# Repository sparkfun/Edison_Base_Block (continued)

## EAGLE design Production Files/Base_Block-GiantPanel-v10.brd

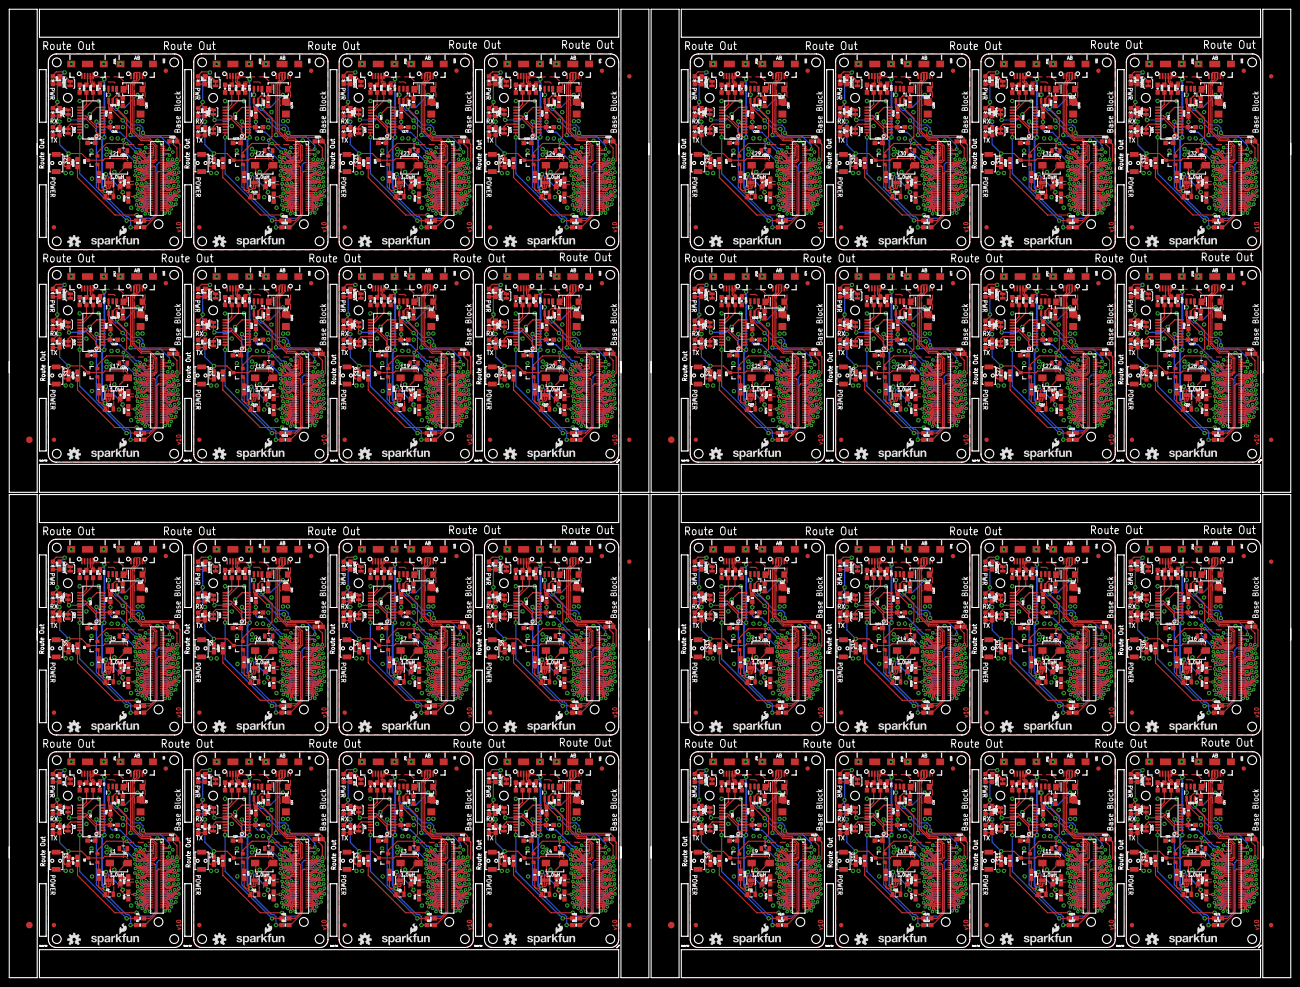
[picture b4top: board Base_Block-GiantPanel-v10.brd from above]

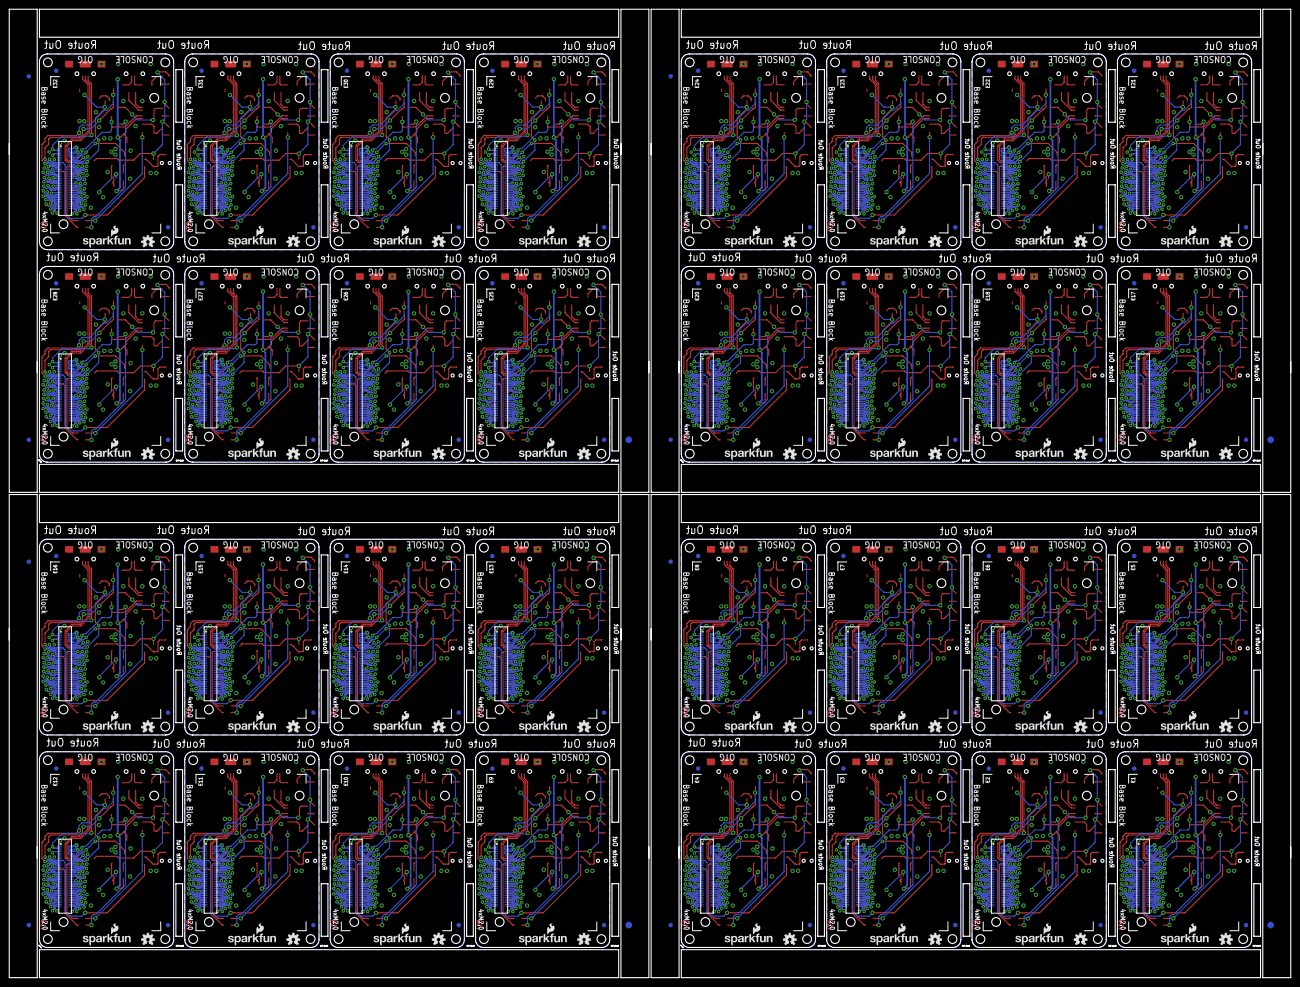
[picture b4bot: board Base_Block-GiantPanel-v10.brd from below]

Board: 2 copper layers, 291.1 x 220.0 mm, 1560 parts (204 on the bottom side), 2496 nets.

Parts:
C1, C2, C5, C10, C17, C18, C25, C26, C33, C34, C41, C42, C49, C50, C57, C58, C65, C66, C73, C74, C81, C82, C89, C90, C97, C98, C105, C106, C113, C114, C121, C122, C129, C130, C137, C138, C145, C146, C153, C154, C161, C162, C169, C170, C177, C178, C185, C186, C193, C194, C201, C202, C209, C210, C217, C218, C225, C226, C233, C234, C241, C242, C249, C250: 0.1uF; 0603-CAP
C3, C4, C7, C11, C12, C15, C19, C20, C23, C27, C28, C31, C35, C36, C39, C43, C44, C47, C51, C52, C55, C59, C60, C63, C67, C68, C71, C75, C76, C79, C83, C84, C87, C91, C92, C95, C99, C100, C103, C107, C108, C111, C115, C116, C119, C123, C124, C127, C131, C132, C135, C139, C140, C143, C147, C148, C151, C155, C156, C159, C163, C164, C167, C171, C172, C175, C179, C180, C183, C187, C188, C191, C195, C196, C199, C203, C204, C207, C211, C212, C215, C219, C220, C223, C227, C228, C231, C235, C236, C239, C243, C244, C247, C251, C252, C255: 47pF; 0603-CAP
C6, C9, C13, C16, C21, C24, C29, C32, C37, C40, C45, C48, C53, C56, C61, C64, C69, C72, C77, C80, C85, C88, C93, C96, C101, C104, C109, C112, C117, C120, C125, C128, C133, C136, C141, C144, C149, C152, C157, C160, C165, C168, C173, C176, C181, C184, C189, C192, C197, C200, C205, C208, C213, C216, C221, C224, C229, C232, C237, C240, C245, C248, C253, C256: 22uF; 0805
C8, C14, C22, C30, C38, C46, C54, C62, C70, C78, C86, C94, C102, C110, C118, C126, C134, C142, C150, C158, C166, C174, C182, C190, C198, C206, C214, C222, C230, C238, C246, C254: 10uF; 1206
D1, D5, D9, D13, D17, D21, D25, D29, D33, D37, D41, D45, D49, D53, D57, D61, D65, D69, D73, D77, D81, D85, D89, D93, D97, D101, D105, D109, D113, D117, D121, D125: RED; LED-0603
D2, D6, D10, D14, D18, D22, D26, D30, D34, D38, D42, D46, D50, D54, D58, D62, D66, D70, D74, D78, D82, D86, D90, D94, D98, D102, D106, D110, D114, D118, D122, D126: YELLOW; LED-0603
D3, D7, D11, D15, D19, D23, D27, D31, D35, D39, D43, D47, D51, D55, D59, D63, D67, D71, D75, D79, D83, D87, D91, D95, D99, D103, D107, D111, D115, D119, D123, D127: BLUE; LED-0603
D4, D8, D12, D16, D20, D24, D28, D32, D36, D40, D44, D48, D52, D56, D60, D64, D68, D72, D76, D80, D84, D88, D92, D96, D100, D104, D108, D112, D116, D120, D124, D128: SMA-DIODE
E1, E2, E3, E4, E5, E6, E7, E8, E9, E10, E11, E12, E13, E14, E15, E16, E17, E18, E19, E20, E21, E22, E23, E24, E25, E26, E27, E28, E29, E30, E31, E32: EDISON_CONNECTOR_FULLMOUNTING_HOLES; EDISON_DAUGHTER
E$1, E$2, E$9, E$10, E$15, E$16, E$21, E$22: FIDUCIAL-1.5X3
E$3, E$4, E$5, E$6, E$7, E$8, E$11, E$12, E$13, E$14, E$17, E$18, E$19, E$20, E$23, E$24: FIDUCIAL-1X2
FID1, FID2, FID3, FID4, FID5, FID6, FID7, FID8, FID9, FID10, FID11, FID12, FID13, FID14, FID15, FID16, FID17, FID18, FID19, FID20, FID21, FID22, FID23, FID24, FID25, FID26, FID27, FID28, FID29, FID30, FID31, FID32, FID33, FID34, FID35, FID36, FID37, FID38, FID39, FID40, FID41, FID42, FID43, FID44, FID45, FID46, FID47, FID48, FID49, FID50, FID51, FID52, FID53, FID54, FID55, FID56, FID57, FID58, FID59, FID60, FID61, FID62, FID63, FID64, FID65, FID66, FID67, FID68, FID69, FID70, FID71, FID72, FID73, FID74, FID75, FID76, FID77, FID78, FID79, FID80, FID81, FID82, FID83, FID84, FID85, FID86, FID87, FID88, FID89, FID90, FID91, FID92, FID93, FID94, FID95, FID96, FID97, FID98, FID99, FID100, FID101, FID102, FID103, FID104, FID105, FID106, FID107, FID108, FID109, FID110, FID111, FID112, FID113, FID114, FID115, FID116, FID117, FID118, FID119, FID120, FID121, FID122, FID123, FID124, FID125, FID126, FID127, FID128: FIDUCIAL1X2; FIDUCIAL-1X2
JP1, JP2, JP3, JP4, JP5, JP6, JP7, JP8, JP9, JP10, JP11, JP12, JP13, JP14, JP15, JP16, JP17, JP18, JP19, JP20, JP21, JP22, JP23, JP24, JP25, JP26, JP27, JP28, JP29, JP30, JP31, JP32: USB_MICROB; USB-B-MICRO-SMD_V03
L1, L2, L3, L4, L5, L6, L7, L8, L9, L10, L11, L12, L13, L14, L15, L16, L17, L18, L19, L20, L21, L22, L23, L24, L25, L26, L27, L28, L29, L30, L31, L32: 1.0uH; INDUCTOR-SRP4020
LOGO1, LOGO3, LOGO6, LOGO7, LOGO10, LOGO11, LOGO14, LOGO15, LOGO18, LOGO19, LOGO22, LOGO23, LOGO26, LOGO27, LOGO30, LOGO31, LOGO34, LOGO35, LOGO38, LOGO39, LOGO42, LOGO43, LOGO46, LOGO47, LOGO50, LOGO51, LOGO54, LOGO55, LOGO58, LOGO59, LOGO62, LOGO63, LOGO66, LOGO67, LOGO70, LOGO71, LOGO74, LOGO75, LOGO78, LOGO79, LOGO82, LOGO83, LOGO86, LOGO87, LOGO90, LOGO91, LOGO94, LOGO95, LOGO98, LOGO99, LOGO102, LOGO103, LOGO106, LOGO107, LOGO110, LOGO111, LOGO114, LOGO115, LOGO118, LOGO119, LOGO122, LOGO123, LOGO126, LOGO127: SFE_LOGO_NAME_FLAME.1_INCH; SFE_LOGO_NAME_FLAME_.1
LOGO2, LOGO4, LOGO5, LOGO8, LOGO9, LOGO12, LOGO13, LOGO16, LOGO17, LOGO20, LOGO21, LOGO24, LOGO25, LOGO28, LOGO29, LOGO32, LOGO33, LOGO36, LOGO37, LOGO40, LOGO41, LOGO44, LOGO45, LOGO48, LOGO49, LOGO52, LOGO53, LOGO56, LOGO57, LOGO60, LOGO61, LOGO64, LOGO65, LOGO68, LOGO69, LOGO72, LOGO73, LOGO76, LOGO77, LOGO80, LOGO81, LOGO84, LOGO85, LOGO88, LOGO89, LOGO92, LOGO93, LOGO96, LOGO97, LOGO100, LOGO101, LOGO104, LOGO105, LOGO108, LOGO109, LOGO112, LOGO113, LOGO116, LOGO117, LOGO120, LOGO121, LOGO124, LOGO125, LOGO128: OSHW-LOGOS; OSHW-LOGO-S
Q1, Q2, Q3, Q4, Q5, Q6, Q7, Q8, Q9, Q10, Q11, Q12, Q13, Q14, Q15, Q16, Q17, Q18, Q19, Q20, Q21, Q22, Q23, Q24, Q25, Q26, Q27, Q28, Q29, Q30, Q31, Q32: BSS138; SOT23-3
R1, R2, R16, R17, R31, R32, R46, R47, R61, R62, R76, R77, R91, R92, R106, R107, R121, R122, R136, R137, R151, R152, R166, R167, R181, R182, R196, R197, R211, R212, R226, R227, R241, R242, R256, R257, R271, R272, R286, R287, R301, R302, R316, R317, R331, R332, R346, R347, R361, R362, R376, R377, R391, R392, R406, R407, R421, R422, R436, R437, R451, R452, R466, R467: 27; 0603
R3, R4, R5, R15, R18, R19, R20, R30, R33, R34, R35, R45, R48, R49, R50, R60, R63, R64, R65, R75, R78, R79, R80, R90, R93, R94, R95, R105, R108, R109, R110, R120, R123, R124, R125, R135, R138, R139, R140, R150, R153, R154, R155, R165, R168, R169, R170, R180, R183, R184, R185, R195, R198, R199, R200, R210, R213, R214, R215, R225, R228, R229, R230, R240, R243, R244, R245, R255, R258, R259, R260, R270, R273, R274, R275, R285, R288, R289, R290, R300, R303, R304, R305, R315, R318, R319, R320, R330, R333, R334, R335, R345, R348, R349, R350, R360, R363, R364, R365, R375, R378, R379, R380, R390, R393, R394, R395, R405, R408, R409, R410, R420, R423, R424, R425, R435, R438, R439, R440, R450, R453, R454, R455, R465, R468, R469, R470, R480: 1K; 0603-RES
R6, R7, R21, R22, R36, R37, R51, R52, R66, R67, R81, R82, R96, R97, R111, R112, R126, R127, R141, R142, R156, R157, R171, R172, R186, R187, R201, R202, R216, R217, R231, R232, R246, R247, R261, R262, R276, R277, R291, R292, R306, R307, R321, R322, R336, R337, R351, R352, R366, R367, R381, R382, R396, R397, R411, R412, R426, R427, R441, R442, R456, R457, R471, R472: 100; 0603-RES
R8, R11, R23, R26, R38, R41, R53, R56, R68, R71, R83, R86, R98, R101, R113, R116, R128, R131, R143, R146, R158, R161, R173, R176, R188, R191, R203, R206, R218, R221, R233, R236, R248, R251, R263, R266, R278, R281, R293, R296, R308, R311, R323, R326, R338, R341, R353, R356, R368, R371, R383, R386, R398, R401, R413, R416, R428, R431, R443, R446, R458, R461, R473, R476: 10K; 0603-RES
R9, R24, R39, R54, R69, R84, R99, R114, R129, R144, R159, R174, R189, R204, R219, R234, R249, R264, R279, R294, R309, R324, R339, R354, R369, R384, R399, R414, R429, R444, R459, R474: 220; 0603-RES
R10, R25, R40, R55, R70, R85, R100, R115, R130, R145, R160, R175, R190, R205, R220, R235, R250, R265, R280, R295, R310, R325, R340, R355, R370, R385, R400, R415, R430, R445, R460, R475: 287; 0603-RES
R12, R27, R42, R57, R72, R87, R102, R117, R132, R147, R162, R177, R192, R207, R222, R237, R252, R267, R282, R297, R312, R327, R342, R357, R372, R387, R402, R417, R432, R447, R462, R477: 100k; 0603-RES
R13, R28, R43, R58, R73, R88, R103, R118, R133, R148, R163, R178, R193, R208, R223, R238, R253, R268, R283, R298, R313, R328, R343, R358, R373, R388, R403, R418, R433, R448, R463, R478: 680k; 0603-RES
R14, R29, R44, R59, R74, R89, R104, R119, R134, R149, R164, R179, R194, R209, R224, R239, R254, R269, R284, R299, R314, R329, R344, R359, R374, R389, R404, R419, R434, R449, R464, R479: 120k; 0603-RES
S1, S2, S3, S4, S5, S6, S7, S8, S9, S10, S11, S12, S13, S14, S15, S16, S17, S18, S19, S20, S21, S22, S23, S24, S25, S26, S27, S28, S29, S30, S31, S32: POWER; TACTILE_SWITCH-SMD-RIGHT-ANGLE
SJ1, SJ2, SJ3, SJ4, SJ5, SJ6, SJ7, SJ8, SJ9, SJ10, SJ11, SJ12, SJ13, SJ14, SJ15, SJ16, SJ17, SJ18, SJ19, SJ20, SJ21, SJ22, SJ23, SJ24, SJ25, SJ26, SJ27, SJ28, SJ29, SJ30, SJ31, SJ32, SJ33, SJ34, SJ35, SJ36, SJ37, SJ38, SJ39, SJ40, SJ41, SJ42, SJ43, SJ44, SJ45, SJ46, SJ47, SJ48, SJ49, SJ50, SJ51, SJ52, SJ53, SJ54, SJ55, SJ56, SJ57, SJ58, SJ59, SJ60, SJ61, SJ62, SJ63, SJ64, SJ65, SJ66, SJ67, SJ68, SJ69, SJ70, SJ71, SJ72, SJ73, SJ74, SJ75, SJ76, SJ77, SJ78, SJ79, SJ80, SJ81, SJ82, SJ83, SJ84, SJ85, SJ86, SJ87, SJ88, SJ89, SJ90, SJ91, SJ92, SJ93, SJ94, SJ95, SJ96: JUMPER-PAD-2-NC_BY_TRACE; PAD-JUMPER-2-NC_BY_TRACE_YES_SILK
U1, U2, U7, U10, U13, U16, U19, U22, U25, U28, U31, U34, U37, U40, U43, U46, U49, U52, U55, U58, U61, U64, U67, U70, U73, U76, U79, U82, U85, U88, U91, U94: FTS31XS-U; SSOP20_L
U3, U5, U8, U11, U14, U17, U20, U23, U26, U29, U32, U35, U38, U41, U44, U47, U50, U53, U56, U59, U62, U65, U68, U71, U74, U77, U80, U83, U86, U89, U92, U95: USB-AB-MICRO-SMD_V03
U4, U6, U9, U12, U15, U18, U21, U24, U27, U30, U33, U36, U39, U42, U45, U48, U51, U54, U57, U60, U63, U66, U69, U72, U75, U78, U81, U84, U87, U90, U93, U96: TPS62065; WSON-8-PAD
U$1, U$4, U$6, U$8, U$10, U$12, U$14, U$16, U$18, U$20, U$22, U$24, U$26, U$28, U$30, U$32, U$34, U$36, U$38, U$40, U$42, U$44, U$46, U$48, U$50, U$52, U$54, U$56, U$58, U$60, U$62, U$64: MIC2039; SOT23-6
U$2, U$3, U$5, U$7, U$9, U$11, U$13, U$15, U$17, U$19, U$21, U$23, U$25, U$27, U$29, U$31, U$33, U$35, U$37, U$39, U$41, U$43, U$45, U$47, U$49, U$51, U$53, U$55, U$57, U$59, U$61, U$63: EDISON_CONNECTOR_FULLHEADER; DF40C-70DP-0.4(51)

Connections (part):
1.8V: C1.2, E1.12, R11.1, U2.3, U2.14, U$3.12
1.8V1: C5.2, E2.12, R26.1, U1.3, U1.14, U$2.12
1.8V2: C17.2, E3.12, R41.1, U7.3, U7.14, U$5.12
1.8V3: C25.2, E4.12, R56.1, U10.3, U10.14, U$7.12
1.8V4: C33.2, E5.12, R71.1, U13.3, U13.14, U$9.12
1.8V5: C41.2, E6.12, R86.1, U16.3, U16.14, U$11.12
1.8V6: C49.2, E7.12, R101.1, U19.3, U19.14, U$13.12
1.8V7: C57.2, E8.12, R116.1, U22.3, U22.14, U$15.12
1.8V8: C65.2, E9.12, R131.1, U25.3, U25.14, U$17.12
1.8V9: C73.2, E10.12, R146.1, U28.3, U28.14, U$19.12
1.8V10: C81.2, E11.12, R161.1, U31.3, U31.14, U$21.12
1.8V11: C89.2, E12.12, R176.1, U34.3, U34.14, U$23.12
1.8V12: C97.2, E13.12, R191.1, U37.3, U37.14, U$25.12
1.8V13: C105.2, E14.12, R206.1, U40.3, U40.14, U$27.12
1.8V14: C113.2, E15.12, R221.1, U43.3, U43.14, U$29.12
1.8V15: C121.2, E16.12, R236.1, U46.3, U46.14, U$31.12
1.8V16: C129.2, E17.12, R251.1, U49.3, U49.14, U$33.12
1.8V17: C137.2, E18.12, R266.1, U52.3, U52.14, U$35.12
1.8V18: C145.2, E19.12, R281.1, U55.3, U55.14, U$37.12
1.8V19: C153.2, E20.12, R296.1, U58.3, U58.14, U$39.12
1.8V20: C161.2, E21.12, R311.1, U61.3, U61.14, U$41.12
1.8V21: C169.2, E22.12, R326.1, U64.3, U64.14, U$43.12
1.8V22: C177.2, E23.12, R341.1, U67.3, U67.14, U$45.12
1.8V23: C185.2, E24.12, R356.1, U70.3, U70.14, U$47.12
1.8V24: C193.2, E25.12, R371.1, U73.3, U73.14, U$49.12
1.8V25: C201.2, E26.12, R386.1, U76.3, U76.14, U$51.12
1.8V26: C209.2, E27.12, R401.1, U79.3, U79.14, U$53.12
1.8V27: C217.2, E28.12, R416.1, U82.3, U82.14, U$55.12
1.8V28: C225.2, E29.12, R431.1, U85.3, U85.14, U$57.12
1.8V29: C233.2, E30.12, R446.1, U88.3, U88.14, U$59.12
1.8V30: C241.2, E31.12, R461.1, U91.3, U91.14, U$61.12
1.8V31: C249.2, E32.12, R476.1, U94.3, U94.14, U$63.12
3.3V: E1.8, E1.10, U$3.8, U$3.10
3.3V1: E2.8, E2.10, U$2.8, U$2.10
3.3V2: E3.8, E3.10, U$5.8, U$5.10
3.3V3: E4.8, E4.10, U$7.8, U$7.10
3.3V4: E5.8, E5.10, U$9.8, U$9.10
3.3V5: E6.8, E6.10, U$11.8, U$11.10
3.3V6: E7.8, E7.10, U$13.8, U$13.10
3.3V7: E8.8, E8.10, U$15.8, U$15.10
3.3V8: E9.8, E9.10, U$17.8, U$17.10
3.3V9: E10.8, E10.10, U$19.8, U$19.10
3.3V10: E11.8, E11.10, U$21.8, U$21.10
3.3V11: E12.8, E12.10, U$23.8, U$23.10
3.3V12: E13.8, E13.10, U$25.8, U$25.10
3.3V13: E14.8, E14.10, U$27.8, U$27.10
3.3V14: E15.8, E15.10, U$29.8, U$29.10
3.3V15: E16.8, E16.10, U$31.8, U$31.10
3.3V16: E17.8, E17.10, U$33.8, U$33.10
3.3V17: E18.8, E18.10, U$35.8, U$35.10
3.3V18: E19.8, E19.10, U$37.8, U$37.10
3.3V19: E20.8, E20.10, U$39.8, U$39.10
3.3V20: E21.8, E21.10, U$41.8, U$41.10
3.3V21: E22.8, E22.10, U$43.8, U$43.10
3.3V22: E23.8, E23.10, U$45.8, U$45.10
3.3V23: E24.8, E24.10, U$47.8, U$47.10
3.3V24: E25.8, E25.10, U$49.8, U$49.10
3.3V25: E26.8, E26.10, U$51.8, U$51.10
3.3V26: E27.8, E27.10, U$53.8, U$53.10
3.3V27: E28.8, E28.10, U$55.8, U$55.10
3.3V28: E29.8, E29.10, U$57.8, U$57.10
3.3V29: E30.8, E30.10, U$59.8, U$59.10
3.3V30: E31.8, E31.10, U$61.8, U$61.10
3.3V31: E32.8, E32.10, U$63.8, U$63.10
5V: C2.2, C9.1, D4.C, JP1.VBUS1, R15.2, U2.15, U4.5, U4.7, U4.8, U$1.1
5V1: C10.2, C16.1, D8.C, JP2.VBUS1, R30.2, U1.15, U6.5, U6.7, U6.8, U$4.1
5V2: C18.2, C24.1, D12.C, JP3.VBUS1, R45.2, U7.15, U9.5, U9.7, U9.8, U$6.1
5V3: C26.2, C32.1, D16.C, JP4.VBUS1, R60.2, U10.15, U12.5, U12.7, U12.8, U$8.1
5V4: C34.2, C40.1, D20.C, JP5.VBUS1, R75.2, U13.15, U15.5, U15.7, U15.8, U$10.1
5V5: C42.2, C48.1, D24.C, JP6.VBUS1, R90.2, U16.15, U18.5, U18.7, U18.8, U$12.1
5V6: C50.2, C56.1, D28.C, JP7.VBUS1, R105.2, U19.15, U21.5, U21.7, U21.8, U$14.1
5V7: C58.2, C64.1, D32.C, JP8.VBUS1, R120.2, U22.15, U24.5, U24.7, U24.8, U$16.1
5V8: C66.2, C72.1, D36.C, JP9.VBUS1, R135.2, U25.15, U27.5, U27.7, U27.8, U$18.1
5V9: C74.2, C80.1, D40.C, JP10.VBUS1, R150.2, U28.15, U30.5, U30.7, U30.8, U$20.1
5V10: C82.2, C88.1, D44.C, JP11.VBUS1, R165.2, U31.15, U33.5, U33.7, U33.8, U$22.1
5V11: C90.2, C96.1, D48.C, JP12.VBUS1, R180.2, U34.15, U36.5, U36.7, U36.8, U$24.1
5V12: C98.2, C104.1, D52.C, JP13.VBUS1, R195.2, U37.15, U39.5, U39.7, U39.8, U$26.1
5V13: C106.2, C112.1, D56.C, JP14.VBUS1, R210.2, U40.15, U42.5, U42.7, U42.8, U$28.1
5V14: C114.2, C120.1, D60.C, JP15.VBUS1, R225.2, U43.15, U45.5, U45.7, U45.8, U$30.1
5V15: C122.2, C128.1, D64.C, JP16.VBUS1, R240.2, U46.15, U48.5, U48.7, U48.8, U$32.1
5V16: C130.2, C136.1, D68.C, JP17.VBUS1, R255.2, U49.15, U51.5, U51.7, U51.8, U$34.1
5V17: C138.2, C144.1, D72.C, JP18.VBUS1, R270.2, U52.15, U54.5, U54.7, U54.8, U$36.1
5V18: C146.2, C152.1, D76.C, JP19.VBUS1, R285.2, U55.15, U57.5, U57.7, U57.8, U$38.1
5V19: C154.2, C160.1, D80.C, JP20.VBUS1, R300.2, U58.15, U60.5, U60.7, U60.8, U$40.1
5V20: C162.2, C168.1, D84.C, JP21.VBUS1, R315.2, U61.15, U63.5, U63.7, U63.8, U$42.1
5V21: C170.2, C176.1, D88.C, JP22.VBUS1, R330.2, U64.15, U66.5, U66.7, U66.8, U$44.1
5V22: C178.2, C184.1, D92.C, JP23.VBUS1, R345.2, U67.15, U69.5, U69.7, U69.8, U$46.1
5V23: C186.2, C192.1, D96.C, JP24.VBUS1, R360.2, U70.15, U72.5, U72.7, U72.8, U$48.1
5V24: C194.2, C200.1, D100.C, JP25.VBUS1, R375.2, U73.15, U75.5, U75.7, U75.8, U$50.1
5V25: C202.2, C208.1, D104.C, JP26.VBUS1, R390.2, U76.15, U78.5, U78.7, U78.8, U$52.1
5V26: C210.2, C216.1, D108.C, JP27.VBUS1, R405.2, U79.15, U81.5, U81.7, U81.8, U$54.1
5V27: C218.2, C224.1, D112.C, JP28.VBUS1, R420.2, U82.15, U84.5, U84.7, U84.8, U$56.1
5V28: C226.2, C232.1, D116.C, JP29.VBUS1, R435.2, U85.15, U87.5, U87.7, U87.8, U$58.1
5V29: C234.2, C240.1, D120.C, JP30.VBUS1, R450.2, U88.15, U90.5, U90.7, U90.8, U$60.1
5V30: C242.2, C248.1, D124.C, JP31.VBUS1, R465.2, U91.15, U93.5, U93.7, U93.8, U$62.1
5V31: C250.2, C256.1, D128.C, JP32.VBUS1, R480.2, U94.15, U96.5, U96.7, U96.8, U$64.1
DCIN: E1.14, Q1.2, U$3.14
DCIN1: E2.14, Q2.2, U$2.14
DCIN2: E3.14, Q3.2, U$5.14
DCIN3: E4.14, Q4.2, U$7.14
DCIN4: E5.14, Q5.2, U$9.14
DCIN5: E6.14, Q6.2, U$11.14
DCIN6: E7.14, Q7.2, U$13.14
DCIN7: E8.14, Q8.2, U$15.14
DCIN8: E9.14, Q9.2, U$17.14
DCIN9: E10.14, Q10.2, U$19.14
DCIN10: E11.14, Q11.2, U$21.14
DCIN11: E12.14, Q12.2, U$23.14
DCIN12: E13.14, Q13.2, U$25.14
DCIN13: E14.14, Q14.2, U$27.14
DCIN14: E15.14, Q15.2, U$29.14
DCIN15: E16.14, Q16.2, U$31.14
DCIN16: E17.14, Q17.2, U$33.14
DCIN17: E18.14, Q18.2, U$35.14
DCIN18: E19.14, Q19.2, U$37.14
DCIN19: E20.14, Q20.2, U$39.14
DCIN20: E21.14, Q21.2, U$41.14
DCIN21: E22.14, Q22.2, U$43.14
DCIN22: E23.14, Q23.2, U$45.14
DCIN23: E24.14, Q24.2, U$47.14
DCIN24: E25.14, Q25.2, U$49.14
DCIN25: E26.14, Q26.2, U$51.14
DCIN26: E27.14, Q27.2, U$53.14
DCIN27: E28.14, Q28.2, U$55.14
DCIN28: E29.14, Q29.2, U$57.14
DCIN29: E30.14, Q30.2, U$59.14
DCIN30: E31.14, Q31.2, U$61.14
DCIN31: E32.14, Q32.2, U$63.14
FAULT: E1.19, R11.2, U$1.4, U$3.19
FAULT1: E2.19, R26.2, U$2.19, U$4.4
FAULT2: E3.19, R41.2, U$5.19, U$6.4
FAULT3: E4.19, R56.2, U$7.19, U$8.4
FAULT4: E5.19, R71.2, U$9.19, U$10.4
FAULT5: E6.19, R86.2, U$11.19, U$12.4
FAULT6: E7.19, R101.2, U$13.19, U$14.4
FAULT7: E8.19, R116.2, U$15.19, U$16.4
FAULT8: E9.19, R131.2, U$17.19, U$18.4
FAULT9: E10.19, R146.2, U$19.19, U$20.4
FAULT10: E11.19, R161.2, U$21.19, U$22.4
FAULT11: E12.19, R176.2, U$23.19, U$24.4
FAULT12: E13.19, R191.2, U$25.19, U$26.4
FAULT13: E14.19, R206.2, U$27.19, U$28.4
FAULT14: E15.19, R221.2, U$29.19, U$30.4
FAULT15: E16.19, R236.2, U$31.19, U$32.4
FAULT16: E17.19, R251.2, U$33.19, U$34.4
FAULT17: E18.19, R266.2, U$35.19, U$36.4
FAULT18: E19.19, R281.2, U$37.19, U$38.4
FAULT19: E20.19, R296.2, U$39.19, U$40.4
FAULT20: E21.19, R311.2, U$41.19, U$42.4
FAULT21: E22.19, R326.2, U$43.19, U$44.4
FAULT22: E23.19, R341.2, U$45.19, U$46.4
FAULT23: E24.19, R356.2, U$47.19, U$48.4
FAULT24: E25.19, R371.2, U$49.19, U$50.4
FAULT25: E26.19, R386.2, U$51.19, U$52.4
FAULT26: E27.19, R401.2, U$53.19, U$54.4
FAULT27: E28.19, R416.2, U$55.19, U$56.4
FAULT28: E29.19, R431.2, U$57.19, U$58.4
FAULT29: E30.19, R446.2, U$59.19, U$60.4
FAULT30: E31.19, R461.2, U$61.19, U$62.4
FAULT31: E32.19, R476.2, U$63.19, U$64.4
FW_RCVR: E1.69, U$3.69
FW_RCVR1: E2.69, U$2.69
FW_RCVR2: E3.69, U$5.69
FW_RCVR3: E4.69, U$7.69
FW_RCVR4: E5.69, U$9.69
FW_RCVR5: E6.69, U$11.69
FW_RCVR6: E7.69, U$13.69
FW_RCVR7: E8.69, U$15.69
FW_RCVR8: E9.69, U$17.69
FW_RCVR9: E10.69, U$19.69
FW_RCVR10: E11.69, U$21.69
FW_RCVR11: E12.69, U$23.69
FW_RCVR12: E13.69, U$25.69
FW_RCVR13: E14.69, U$27.69
FW_RCVR14: E15.69, U$29.69
FW_RCVR15: E16.69, U$31.69
FW_RCVR16: E17.69, U$33.69
FW_RCVR17: E18.69, U$35.69
FW_RCVR18: E19.69, U$37.69
FW_RCVR19: E20.69, U$39.69
FW_RCVR20: E21.69, U$41.69
FW_RCVR21: E22.69, U$43.69
FW_RCVR22: E23.69, U$45.69
FW_RCVR23: E24.69, U$47.69
FW_RCVR24: E25.69, U$49.69
FW_RCVR25: E26.69, U$51.69
FW_RCVR26: E27.69, U$53.69
FW_RCVR27: E28.69, U$55.69
FW_RCVR28: E29.69, U$57.69
FW_RCVR29: E30.69, U$59.69
FW_RCVR30: E31.69, U$61.69
FW_RCVR31: E32.69, U$63.69
GND: C1.1, C2.1, C3.2, C4.2, C6.2, C8.2, C9.2, E1.1, E1.5, E1.9, E1.11, E1.13, E1.15, JP1.GND1, JP1.SHIELD1, JP1.SHIELD2, JP1.SHIELD3, R10.1, R12.1, R14.1, S1.2, SJ3.1, U2.6, U2.16, U3.GND1, U4.1, U4.3, U4.6, U4.PAD, U$1.2, U$3.1, U$3.5, U$3.9, U$3.11, U$3.13, U$3.15
GND1: C5.1, C10.1, C11.2, C12.2, C13.2, C14.2, C16.2, E2.1, E2.5, E2.9, E2.11, E2.13, E2.15, JP2.GND1, JP2.SHIELD1, JP2.SHIELD2, JP2.SHIELD3, R25.1, R27.1, R29.1, S2.2, SJ6.1, U1.6, U1.16, U5.GND1, U6.1, U6.3, U6.6, U6.PAD, U$2.1, U$2.5, U$2.9, U$2.11, U$2.13, U$2.15, U$4.2
GND2: C17.1, C18.1, C19.2, C20.2, C21.2, C22.2, C24.2, E3.1, E3.5, E3.9, E3.11, E3.13, E3.15, JP3.GND1, JP3.SHIELD1, JP3.SHIELD2, JP3.SHIELD3, R40.1, R42.1, R44.1, S3.2, SJ9.1, U7.6, U7.16, U8.GND1, U9.1, U9.3, U9.6, U9.PAD, U$5.1, U$5.5, U$5.9, U$5.11, U$5.13, U$5.15, U$6.2
GND3: C25.1, C26.1, C27.2, C28.2, C29.2, C30.2, C32.2, E4.1, E4.5, E4.9, E4.11, E4.13, E4.15, JP4.GND1, JP4.SHIELD1, JP4.SHIELD2, JP4.SHIELD3, R55.1, R57.1, R59.1, S4.2, SJ12.1, U10.6, U10.16, U11.GND1, U12.1, U12.3, U12.6, U12.PAD, U$7.1, U$7.5, U$7.9, U$7.11, U$7.13, U$7.15, U$8.2
GND4: C33.1, C34.1, C35.2, C36.2, C37.2, C38.2, C40.2, E5.1, E5.5, E5.9, E5.11, E5.13, E5.15, JP5.GND1, JP5.SHIELD1, JP5.SHIELD2, JP5.SHIELD3, R70.1, R72.1, R74.1, S5.2, SJ15.1, U13.6, U13.16, U14.GND1, U15.1, U15.3, U15.6, U15.PAD, U$9.1, U$9.5, U$9.9, U$9.11, U$9.13, U$9.15, U$10.2
GND5: C41.1, C42.1, C43.2, C44.2, C45.2, C46.2, C48.2, E6.1, E6.5, E6.9, E6.11, E6.13, E6.15, JP6.GND1, JP6.SHIELD1, JP6.SHIELD2, JP6.SHIELD3, R85.1, R87.1, R89.1, S6.2, SJ18.1, U16.6, U16.16, U17.GND1, U18.1, U18.3, U18.6, U18.PAD, U$11.1, U$11.5, U$11.9, U$11.11, U$11.13, U$11.15, U$12.2
GND6: C49.1, C50.1, C51.2, C52.2, C53.2, C54.2, C56.2, E7.1, E7.5, E7.9, E7.11, E7.13, E7.15, JP7.GND1, JP7.SHIELD1, JP7.SHIELD2, JP7.SHIELD3, R100.1, R102.1, R104.1, S7.2, SJ21.1, U19.6, U19.16, U20.GND1, U21.1, U21.3, U21.6, U21.PAD, U$13.1, U$13.5, U$13.9, U$13.11, U$13.13, U$13.15, U$14.2
GND7: C57.1, C58.1, C59.2, C60.2, C61.2, C62.2, C64.2, E8.1, E8.5, E8.9, E8.11, E8.13, E8.15, JP8.GND1, JP8.SHIELD1, JP8.SHIELD2, JP8.SHIELD3, R115.1, R117.1, R119.1, S8.2, SJ24.1, U22.6, U22.16, U23.GND1, U24.1, U24.3, U24.6, U24.PAD, U$15.1, U$15.5, U$15.9, U$15.11, U$15.13, U$15.15, U$16.2
GND8: C65.1, C66.1, C67.2, C68.2, C69.2, C70.2, C72.2, E9.1, E9.5, E9.9, E9.11, E9.13, E9.15, JP9.GND1, JP9.SHIELD1, JP9.SHIELD2, JP9.SHIELD3, R130.1, R132.1, R134.1, S9.2, SJ27.1, U25.6, U25.16, U26.GND1, U27.1, U27.3, U27.6, U27.PAD, U$17.1, U$17.5, U$17.9, U$17.11, U$17.13, U$17.15, U$18.2
GND9: C73.1, C74.1, C75.2, C76.2, C77.2, C78.2, C80.2, E10.1, E10.5, E10.9, E10.11, E10.13, E10.15, JP10.GND1, JP10.SHIELD1, JP10.SHIELD2, JP10.SHIELD3, R145.1, R147.1, R149.1, S10.2, SJ30.1, U28.6, U28.16, U29.GND1, U30.1, U30.3, U30.6, U30.PAD, U$19.1, U$19.5, U$19.9, U$19.11, U$19.13, U$19.15, U$20.2
GND10: C81.1, C82.1, C83.2, C84.2, C85.2, C86.2, C88.2, E11.1, E11.5, E11.9, E11.11, E11.13, E11.15, JP11.GND1, JP11.SHIELD1, JP11.SHIELD2, JP11.SHIELD3, R160.1, R162.1, R164.1, S11.2, SJ33.1, U31.6, U31.16, U32.GND1, U33.1, U33.3, U33.6, U33.PAD, U$21.1, U$21.5, U$21.9, U$21.11, U$21.13, U$21.15, U$22.2
GND11: C89.1, C90.1, C91.2, C92.2, C93.2, C94.2, C96.2, E12.1, E12.5, E12.9, E12.11, E12.13, E12.15, JP12.GND1, JP12.SHIELD1, JP12.SHIELD2, JP12.SHIELD3, R175.1, R177.1, R179.1, S12.2, SJ36.1, U34.6, U34.16, U35.GND1, U36.1, U36.3, U36.6, U36.PAD, U$23.1, U$23.5, U$23.9, U$23.11, U$23.13, U$23.15, U$24.2
GND12: C97.1, C98.1, C99.2, C100.2, C101.2, C102.2, C104.2, E13.1, E13.5, E13.9, E13.11, E13.13, E13.15, JP13.GND1, JP13.SHIELD1, JP13.SHIELD2, JP13.SHIELD3, R190.1, R192.1, R194.1, S13.2, SJ39.1, U37.6, U37.16, U38.GND1, U39.1, U39.3, U39.6, U39.PAD, U$25.1, U$25.5, U$25.9, U$25.11, U$25.13, U$25.15, U$26.2
GND13: C105.1, C106.1, C107.2, C108.2, C109.2, C110.2, C112.2, E14.1, E14.5, E14.9, E14.11, E14.13, E14.15, JP14.GND1, JP14.SHIELD1, JP14.SHIELD2, JP14.SHIELD3, R205.1, R207.1, R209.1, S14.2, SJ42.1, U40.6, U40.16, U41.GND1, U42.1, U42.3, U42.6, U42.PAD, U$27.1, U$27.5, U$27.9, U$27.11, U$27.13, U$27.15, U$28.2
GND14: C113.1, C114.1, C115.2, C116.2, C117.2, C118.2, C120.2, E15.1, E15.5, E15.9, E15.11, E15.13, E15.15, JP15.GND1, JP15.SHIELD1, JP15.SHIELD2, JP15.SHIELD3, R220.1, R222.1, R224.1, S15.2, SJ45.1, U43.6, U43.16, U44.GND1, U45.1, U45.3, U45.6, U45.PAD, U$29.1, U$29.5, U$29.9, U$29.11, U$29.13, U$29.15, U$30.2
GND15: C121.1, C122.1, C123.2, C124.2, C125.2, C126.2, C128.2, E16.1, E16.5, E16.9, E16.11, E16.13, E16.15, JP16.GND1, JP16.SHIELD1, JP16.SHIELD2, JP16.SHIELD3, R235.1, R237.1, R239.1, S16.2, SJ48.1, U46.6, U46.16, U47.GND1, U48.1, U48.3, U48.6, U48.PAD, U$31.1, U$31.5, U$31.9, U$31.11, U$31.13, U$31.15, U$32.2
GND16: C129.1, C130.1, C131.2, C132.2, C133.2, C134.2, C136.2, E17.1, E17.5, E17.9, E17.11, E17.13, E17.15, JP17.GND1, JP17.SHIELD1, JP17.SHIELD2, JP17.SHIELD3, R250.1, R252.1, R254.1, S17.2, SJ51.1, U49.6, U49.16, U50.GND1, U51.1, U51.3, U51.6, U51.PAD, U$33.1, U$33.5, U$33.9, U$33.11, U$33.13, U$33.15, U$34.2
GND17: C137.1, C138.1, C139.2, C140.2, C141.2, C142.2, C144.2, E18.1, E18.5, E18.9, E18.11, E18.13, E18.15, JP18.GND1, JP18.SHIELD1, JP18.SHIELD2, JP18.SHIELD3, R265.1, R267.1, R269.1, S18.2, SJ54.1, U52.6, U52.16, U53.GND1, U54.1, U54.3, U54.6, U54.PAD, U$35.1, U$35.5, U$35.9, U$35.11, U$35.13, U$35.15, U$36.2
GND18: C145.1, C146.1, C147.2, C148.2, C149.2, C150.2, C152.2, E19.1, E19.5, E19.9, E19.11, E19.13, E19.15, JP19.GND1, JP19.SHIELD1, JP19.SHIELD2, JP19.SHIELD3, R280.1, R282.1, R284.1, S19.2, SJ57.1, U55.6, U55.16, U56.GND1, U57.1, U57.3, U57.6, U57.PAD, U$37.1, U$37.5, U$37.9, U$37.11, U$37.13, U$37.15, U$38.2
GND19: C153.1, C154.1, C155.2, C156.2, C157.2, C158.2, C160.2, E20.1, E20.5, E20.9, E20.11, E20.13, E20.15, JP20.GND1, JP20.SHIELD1, JP20.SHIELD2, JP20.SHIELD3, R295.1, R297.1, R299.1, S20.2, SJ60.1, U58.6, U58.16, U59.GND1, U60.1, U60.3, U60.6, U60.PAD, U$39.1, U$39.5, U$39.9, U$39.11, U$39.13, U$39.15, U$40.2
GND20: C161.1, C162.1, C163.2, C164.2, C165.2, C166.2, C168.2, E21.1, E21.5, E21.9, E21.11, E21.13, E21.15, JP21.GND1, JP21.SHIELD1, JP21.SHIELD2, JP21.SHIELD3, R310.1, R312.1, R314.1, S21.2, SJ63.1, U61.6, U61.16, U62.GND1, U63.1, U63.3, U63.6, U63.PAD, U$41.1, U$41.5, U$41.9, U$41.11, U$41.13, U$41.15, U$42.2
GND21: C169.1, C170.1, C171.2, C172.2, C173.2, C174.2, C176.2, E22.1, E22.5, E22.9, E22.11, E22.13, E22.15, JP22.GND1, JP22.SHIELD1, JP22.SHIELD2, JP22.SHIELD3, R325.1, R327.1, R329.1, S22.2, SJ66.1, U64.6, U64.16, U65.GND1, U66.1, U66.3, U66.6, U66.PAD, U$43.1, U$43.5, U$43.9, U$43.11, U$43.13, U$43.15, U$44.2
GND22: C177.1, C178.1, C179.2, C180.2, C181.2, C182.2, C184.2, E23.1, E23.5, E23.9, E23.11, E23.13, E23.15, JP23.GND1, JP23.SHIELD1, JP23.SHIELD2, JP23.SHIELD3, R340.1, R342.1, R344.1, S23.2, SJ69.1, U67.6, U67.16, U68.GND1, U69.1, U69.3, U69.6, U69.PAD, U$45.1, U$45.5, U$45.9, U$45.11, U$45.13, U$45.15, U$46.2
GND23: C185.1, C186.1, C187.2, C188.2, C189.2, C190.2, C192.2, E24.1, E24.5, E24.9, E24.11, E24.13, E24.15, JP24.GND1, JP24.SHIELD1, JP24.SHIELD2, JP24.SHIELD3, R355.1, R357.1, R359.1, S24.2, SJ72.1, U70.6, U70.16, U71.GND1, U72.1, U72.3, U72.6, U72.PAD, U$47.1, U$47.5, U$47.9, U$47.11, U$47.13, U$47.15, U$48.2
GND24: C193.1, C194.1, C195.2, C196.2, C197.2, C198.2, C200.2, E25.1, E25.5, E25.9, E25.11, E25.13, E25.15, JP25.GND1, JP25.SHIELD1, JP25.SHIELD2, JP25.SHIELD3, R370.1, R372.1, R374.1, S25.2, SJ75.1, U73.6, U73.16, U74.GND1, U75.1, U75.3, U75.6, U75.PAD, U$49.1, U$49.5, U$49.9, U$49.11, U$49.13, U$49.15, U$50.2
GND25: C201.1, C202.1, C203.2, C204.2, C205.2, C206.2, C208.2, E26.1, E26.5, E26.9, E26.11, E26.13, E26.15, JP26.GND1, JP26.SHIELD1, JP26.SHIELD2, JP26.SHIELD3, R385.1, R387.1, R389.1, S26.2, SJ78.1, U76.6, U76.16, U77.GND1, U78.1, U78.3, U78.6, U78.PAD, U$51.1, U$51.5, U$51.9, U$51.11, U$51.13, U$51.15, U$52.2
GND26: C209.1, C210.1, C211.2, C212.2, C213.2, C214.2, C216.2, E27.1, E27.5, E27.9, E27.11, E27.13, E27.15, JP27.GND1, JP27.SHIELD1, JP27.SHIELD2, JP27.SHIELD3, R400.1, R402.1, R404.1, S27.2, SJ81.1, U79.6, U79.16, U80.GND1, U81.1, U81.3, U81.6, U81.PAD, U$53.1, U$53.5, U$53.9, U$53.11, U$53.13, U$53.15, U$54.2
GND27: C217.1, C218.1, C219.2, C220.2, C221.2, C222.2, C224.2, E28.1, E28.5, E28.9, E28.11, E28.13, E28.15, JP28.GND1, JP28.SHIELD1, JP28.SHIELD2, JP28.SHIELD3, R415.1, R417.1, R419.1, S28.2, SJ84.1, U82.6, U82.16, U83.GND1, U84.1, U84.3, U84.6, U84.PAD, U$55.1, U$55.5, U$55.9, U$55.11, U$55.13, U$55.15, U$56.2
GND28: C225.1, C226.1, C227.2, C228.2, C229.2, C230.2, C232.2, E29.1, E29.5, E29.9, E29.11, E29.13, E29.15, JP29.GND1, JP29.SHIELD1, JP29.SHIELD2, JP29.SHIELD3, R430.1, R432.1, R434.1, S29.2, SJ87.1, U85.6, U85.16, U86.GND1, U87.1, U87.3, U87.6, U87.PAD, U$57.1, U$57.5, U$57.9, U$57.11, U$57.13, U$57.15, U$58.2
GND29: C233.1, C234.1, C235.2, C236.2, C237.2, C238.2, C240.2, E30.1, E30.5, E30.9, E30.11, E30.13, E30.15, JP30.GND1, JP30.SHIELD1, JP30.SHIELD2, JP30.SHIELD3, R445.1, R447.1, R449.1, S30.2, SJ90.1, U88.6, U88.16, U89.GND1, U90.1, U90.3, U90.6, U90.PAD, U$59.1, U$59.5, U$59.9, U$59.11, U$59.13, U$59.15, U$60.2
GND30: C241.1, C242.1, C243.2, C244.2, C245.2, C246.2, C248.2, E31.1, E31.5, E31.9, E31.11, E31.13, E31.15, JP31.GND1, JP31.SHIELD1, JP31.SHIELD2, JP31.SHIELD3, R460.1, R462.1, R464.1, S31.2, SJ93.1, U91.6, U91.16, U92.GND1, U93.1, U93.3, U93.6, U93.PAD, U$61.1, U$61.5, U$61.9, U$61.11, U$61.13, U$61.15, U$62.2
GND31: C249.1, C250.1, C251.2, C252.2, C253.2, C254.2, C256.2, E32.1, E32.5, E32.9, E32.11, E32.13, E32.15, JP32.GND1, JP32.SHIELD1, JP32.SHIELD2, JP32.SHIELD3, R475.1, R477.1, R479.1, S32.2, SJ96.1, U94.6, U94.16, U95.GND1, U96.1, U96.3, U96.6, U96.PAD, U$63.1, U$63.5, U$63.9, U$63.11, U$63.13, U$63.15, U$64.2
GP1: E2.48, U$2.48
GP2: E2.42, U$2.42
GP3: E2.34, U$2.34
GP4: E2.32, U$2.32
GP5: E2.30, U$2.30
GP6: E2.28, U$2.28
GP7: E2.26, U$2.26
GP8: E2.25, U$2.25
GP9: E2.24, U$2.24
GP10: E3.48, U$5.48
GP11: E3.42, U$5.42
GP12: E3.34, U$5.34
GP12_PWM0: E1.35, U$3.35
GP12_PWM1: E2.35, U$2.35
GP12_PWM2: E3.35, U$5.35
GP12_PWM3: E4.35, U$7.35
GP12_PWM4: E5.35, U$9.35
GP12_PWM5: E6.35, U$11.35
GP12_PWM6: E7.35, U$13.35
GP12_PWM7: E8.35, U$15.35
GP12_PWM8: E9.35, U$17.35
GP12_PWM9: E10.35, U$19.35
GP12_PWM10: E11.35, U$21.35
GP12_PWM11: E12.35, U$23.35
GP12_PWM12: E13.35, U$25.35
GP12_PWM13: E14.35, U$27.35
GP12_PWM14: E15.35, U$29.35
GP12_PWM15: E16.35, U$31.35
GP12_PWM16: E17.35, U$33.35
GP12_PWM17: E18.35, U$35.35
GP12_PWM18: E19.35, U$37.35
GP12_PWM19: E20.35, U$39.35
GP12_PWM20: E21.35, U$41.35
GP12_PWM21: E22.35, U$43.35
GP12_PWM22: E23.35, U$45.35
GP12_PWM23: E24.35, U$47.35
GP12_PWM24: E25.35, U$49.35
GP12_PWM25: E26.35, U$51.35
GP12_PWM26: E27.35, U$53.35
GP12_PWM27: E28.35, U$55.35
GP12_PWM28: E29.35, U$57.35
GP12_PWM29: E30.35, U$59.35
GP12_PWM30: E31.35, U$61.35
GP12_PWM31: E32.35, U$63.35
GP13: E3.32, U$5.32
GP13_PWM1: E1.33, U$3.33
GP13_PWM2: E2.33, U$2.33
GP13_PWM3: E3.33, U$5.33
GP13_PWM4: E4.33, U$7.33
GP13_PWM5: E5.33, U$9.33
GP13_PWM6: E6.33, U$11.33
GP13_PWM7: E7.33, U$13.33
GP13_PWM8: E8.33, U$15.33
GP13_PWM9: E9.33, U$17.33
GP13_PWM10: E10.33, U$19.33
GP13_PWM11: E11.33, U$21.33
GP13_PWM12: E12.33, U$23.33
GP13_PWM13: E13.33, U$25.33
GP13_PWM14: E14.33, U$27.33
GP13_PWM15: E15.33, U$29.33
GP13_PWM16: E16.33, U$31.33
GP13_PWM17: E17.33, U$33.33
GP13_PWM18: E18.33, U$35.33
GP13_PWM19: E19.33, U$37.33
GP13_PWM20: E20.33, U$39.33
GP13_PWM21: E21.33, U$41.33
GP13_PWM22: E22.33, U$43.33
GP13_PWM23: E23.33, U$45.33
GP13_PWM24: E24.33, U$47.33
GP13_PWM25: E25.33, U$49.33
GP13_PWM26: E26.33, U$51.33
GP13_PWM27: E27.33, U$53.33
GP13_PWM28: E28.33, U$55.33
GP13_PWM29: E29.33, U$57.33
GP13_PWM30: E30.33, U$59.33
GP13_PWM31: E31.33, U$61.33
GP13_PWM32: E32.33, U$63.33
GP14: E1.48, U$3.48
GP15: E1.42, U$3.42
GP16: E3.30, U$5.30
GP17: E3.28, U$5.28
GP18: E3.26, U$5.26
GP19: E3.25, U$5.25
GP19_I2C_1_SCL: E1.41, U$3.41
GP19_I2C_1_SCL1: E2.41, U$2.41
GP19_I2C_1_SCL2: E3.41, U$5.41
GP19_I2C_1_SCL3: E4.41, U$7.41
GP19_I2C_1_SCL4: E5.41, U$9.41
GP19_I2C_1_SCL5: E6.41, U$11.41
GP19_I2C_1_SCL6: E7.41, U$13.41
GP19_I2C_1_SCL7: E8.41, U$15.41
GP19_I2C_1_SCL8: E9.41, U$17.41
GP19_I2C_1_SCL9: E10.41, U$19.41
GP19_I2C_1_SCL10: E11.41, U$21.41
GP19_I2C_1_SCL11: E12.41, U$23.41
GP19_I2C_1_SCL12: E13.41, U$25.41
GP19_I2C_1_SCL13: E14.41, U$27.41
GP19_I2C_1_SCL14: E15.41, U$29.41
GP19_I2C_1_SCL15: E16.41, U$31.41
GP19_I2C_1_SCL16: E17.41, U$33.41
GP19_I2C_1_SCL17: E18.41, U$35.41
GP19_I2C_1_SCL18: E19.41, U$37.41
GP19_I2C_1_SCL19: E20.41, U$39.41
GP19_I2C_1_SCL20: E21.41, U$41.41
GP19_I2C_1_SCL21: E22.41, U$43.41
GP19_I2C_1_SCL22: E23.41, U$45.41
GP19_I2C_1_SCL23: E24.41, U$47.41
GP19_I2C_1_SCL24: E25.41, U$49.41
GP19_I2C_1_SCL25: E26.41, U$51.41
GP19_I2C_1_SCL26: E27.41, U$53.41
GP19_I2C_1_SCL27: E28.41, U$55.41
GP19_I2C_1_SCL28: E29.41, U$57.41
GP19_I2C_1_SCL29: E30.41, U$59.41
GP19_I2C_1_SCL30: E31.41, U$61.41
GP19_I2C_1_SCL31: E32.41, U$63.41
GP20: E3.24, U$5.24
GP20_I2C_1_SDA: E1.43, U$3.43
GP20_I2C_1_SDA1: E2.43, U$2.43
GP20_I2C_1_SDA2: E3.43, U$5.43
GP20_I2C_1_SDA3: E4.43, U$7.43
GP20_I2C_1_SDA4: E5.43, U$9.43
GP20_I2C_1_SDA5: E6.43, U$11.43
GP20_I2C_1_SDA6: E7.43, U$13.43
GP20_I2C_1_SDA7: E8.43, U$15.43
GP20_I2C_1_SDA8: E9.43, U$17.43
GP20_I2C_1_SDA9: E10.43, U$19.43
GP20_I2C_1_SDA10: E11.43, U$21.43
GP20_I2C_1_SDA11: E12.43, U$23.43
GP20_I2C_1_SDA12: E13.43, U$25.43
GP20_I2C_1_SDA13: E14.43, U$27.43
GP20_I2C_1_SDA14: E15.43, U$29.43
GP20_I2C_1_SDA15: E16.43, U$31.43
GP20_I2C_1_SDA16: E17.43, U$33.43
GP20_I2C_1_SDA17: E18.43, U$35.43
GP20_I2C_1_SDA18: E19.43, U$37.43
GP20_I2C_1_SDA19: E20.43, U$39.43
GP20_I2C_1_SDA20: E21.43, U$41.43
GP20_I2C_1_SDA21: E22.43, U$43.43
GP20_I2C_1_SDA22: E23.43, U$45.43
GP20_I2C_1_SDA23: E24.43, U$47.43
GP20_I2C_1_SDA24: E25.43, U$49.43
GP20_I2C_1_SDA25: E26.43, U$51.43
GP20_I2C_1_SDA26: E27.43, U$53.43
GP20_I2C_1_SDA27: E28.43, U$55.43
GP20_I2C_1_SDA28: E29.43, U$57.43
GP20_I2C_1_SDA29: E30.43, U$59.43
GP20_I2C_1_SDA30: E31.43, U$61.43
GP20_I2C_1_SDA31: E32.43, U$63.43
GP21: E4.48, U$7.48
GP22: E4.42, U$7.42
GP23: E4.34, U$7.34
GP24: E4.32, U$7.32
GP25: E4.30, U$7.30
GP26: E4.28, U$7.28
GP27: E4.26, U$7.26
GP27_I2C_6_SCL: E1.45, U$3.45
GP27_I2C_6_SCL1: E2.45, U$2.45
GP27_I2C_6_SCL2: E3.45, U$5.45
GP27_I2C_6_SCL3: E4.45, U$7.45
GP27_I2C_6_SCL4: E5.45, U$9.45
GP27_I2C_6_SCL5: E6.45, U$11.45
GP27_I2C_6_SCL6: E7.45, U$13.45
GP27_I2C_6_SCL7: E8.45, U$15.45
GP27_I2C_6_SCL8: E9.45, U$17.45
GP27_I2C_6_SCL9: E10.45, U$19.45
GP27_I2C_6_SCL10: E11.45, U$21.45
GP27_I2C_6_SCL11: E12.45, U$23.45
GP27_I2C_6_SCL12: E13.45, U$25.45
GP27_I2C_6_SCL13: E14.45, U$27.45
GP27_I2C_6_SCL14: E15.45, U$29.45
GP27_I2C_6_SCL15: E16.45, U$31.45
GP27_I2C_6_SCL16: E17.45, U$33.45
GP27_I2C_6_SCL17: E18.45, U$35.45
GP27_I2C_6_SCL18: E19.45, U$37.45
GP27_I2C_6_SCL19: E20.45, U$39.45
GP27_I2C_6_SCL20: E21.45, U$41.45
GP27_I2C_6_SCL21: E22.45, U$43.45
GP27_I2C_6_SCL22: E23.45, U$45.45
GP27_I2C_6_SCL23: E24.45, U$47.45
GP27_I2C_6_SCL24: E25.45, U$49.45
GP27_I2C_6_SCL25: E26.45, U$51.45
GP27_I2C_6_SCL26: E27.45, U$53.45
GP27_I2C_6_SCL27: E28.45, U$55.45
GP27_I2C_6_SCL28: E29.45, U$57.45
GP27_I2C_6_SCL29: E30.45, U$59.45
GP27_I2C_6_SCL30: E31.45, U$61.45
GP27_I2C_6_SCL31: E32.45, U$63.45
GP28: E4.25, U$7.25
GP28_I2C_6_SDA: E1.47, U$3.47
GP28_I2C_6_SDA1: E2.47, U$2.47
GP28_I2C_6_SDA2: E3.47, U$5.47
GP28_I2C_6_SDA3: E4.47, U$7.47
GP28_I2C_6_SDA4: E5.47, U$9.47
GP28_I2C_6_SDA5: E6.47, U$11.47
GP28_I2C_6_SDA6: E7.47, U$13.47
GP28_I2C_6_SDA7: E8.47, U$15.47
GP28_I2C_6_SDA8: E9.47, U$17.47
GP28_I2C_6_SDA9: E10.47, U$19.47
GP28_I2C_6_SDA10: E11.47, U$21.47
GP28_I2C_6_SDA11: E12.47, U$23.47
GP28_I2C_6_SDA12: E13.47, U$25.47
GP28_I2C_6_SDA13: E14.47, U$27.47
GP28_I2C_6_SDA14: E15.47, U$29.47
GP28_I2C_6_SDA15: E16.47, U$31.47
GP28_I2C_6_SDA16: E17.47, U$33.47
GP28_I2C_6_SDA17: E18.47, U$35.47
GP28_I2C_6_SDA18: E19.47, U$37.47
GP28_I2C_6_SDA19: E20.47, U$39.47
GP28_I2C_6_SDA20: E21.47, U$41.47
GP28_I2C_6_SDA21: E22.47, U$43.47
GP28_I2C_6_SDA22: E23.47, U$45.47
GP28_I2C_6_SDA23: E24.47, U$47.47
GP28_I2C_6_SDA24: E25.47, U$49.47
GP28_I2C_6_SDA25: E26.47, U$51.47
GP28_I2C_6_SDA26: E27.47, U$53.47
GP28_I2C_6_SDA27: E28.47, U$55.47
GP28_I2C_6_SDA28: E29.47, U$57.47
GP28_I2C_6_SDA29: E30.47, U$59.47
GP28_I2C_6_SDA30: E31.47, U$61.47
GP28_I2C_6_SDA31: E32.47, U$63.47
GP29: E4.24, U$7.24
GP30: E5.48, U$9.48
GP31: E5.42, U$9.42
GP32: E5.34, U$9.34
GP33: E5.32, U$9.32
GP34: E5.30, U$9.30
GP35: E5.28, U$9.28
GP36: E5.26, U$9.26
GP37: E5.25, U$9.25
GP38: E5.24, U$9.24
GP39: E6.48, U$11.48
GP40: E6.42, U$11.42
GP40_I2S_2_CLK: E1.52, U$3.52
GP40_I2S_2_CLK1: E2.52, U$2.52
GP40_I2S_2_CLK2: E3.52, U$5.52
GP40_I2S_2_CLK3: E4.52, U$7.52
GP40_I2S_2_CLK4: E5.52, U$9.52
GP40_I2S_2_CLK5: E6.52, U$11.52
GP40_I2S_2_CLK6: E7.52, U$13.52
GP40_I2S_2_CLK7: E8.52, U$15.52
GP40_I2S_2_CLK8: E9.52, U$17.52
GP40_I2S_2_CLK9: E10.52, U$19.52
GP40_I2S_2_CLK10: E11.52, U$21.52
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
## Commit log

2014-06-27 added hardware
2014-06-30 added gitignore
2014-06-30 git ignore
2014-06-30 deleted: Hardware/TestRig.s##
2014-06-30 file cleanup
2014-08-05 added template board
2014-08-08 completed base layout, ready for review. Removed testing layouts and other noise
2014-08-08 changed out power supply for something more powerful. Added fiducials
2014-08-09 moved USB connector to give room for larger cables
2014-08-12 removed Edzzanine from name
2014-09-23 Corrected OTG power issue Corrected name and position added DCIN pin to connector Added DCIN enable circuit corrected dimensions and cleaned up drawings replaced power button with new SMD side shooti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
2014-09-23 changed names of boards
2014-10-17 Modified Footprint for connectors, removed jumpers. changed version number corrected silk moved diode to help AOI removed jumpers from power supply replaced input and output capacitors on power suppl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
2014-10-17 Minor touchups for reds
2014-10-17 Ready for reds. Minor silk change. No known to-do items
2014-10-21 added bottom side fids
2014-10-22 created v10 panels
